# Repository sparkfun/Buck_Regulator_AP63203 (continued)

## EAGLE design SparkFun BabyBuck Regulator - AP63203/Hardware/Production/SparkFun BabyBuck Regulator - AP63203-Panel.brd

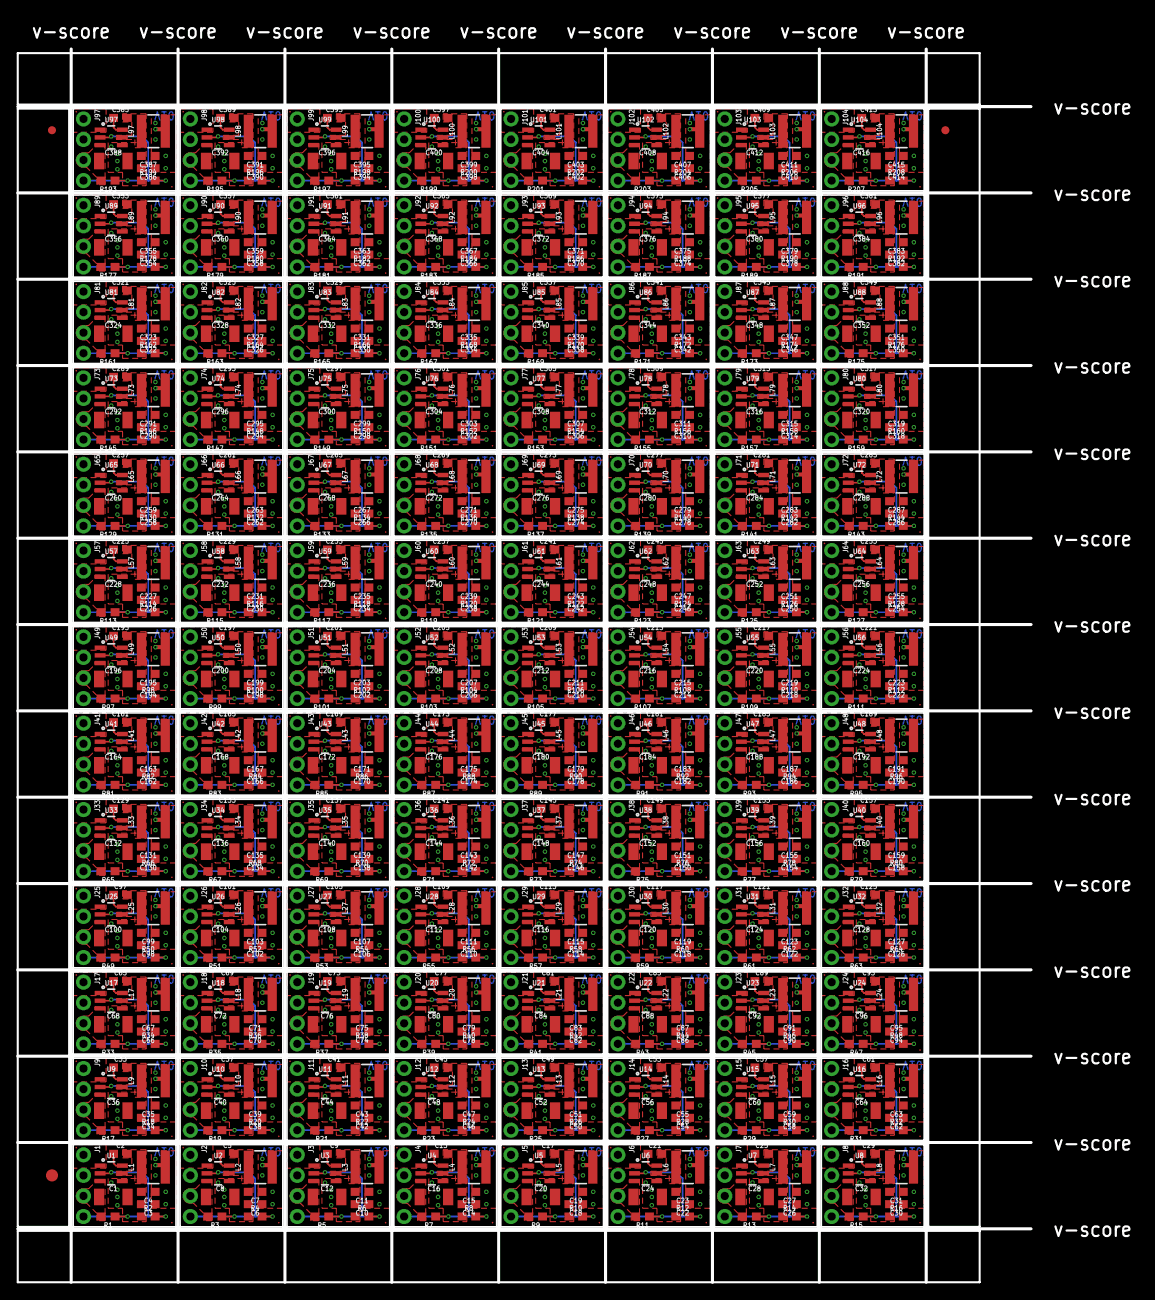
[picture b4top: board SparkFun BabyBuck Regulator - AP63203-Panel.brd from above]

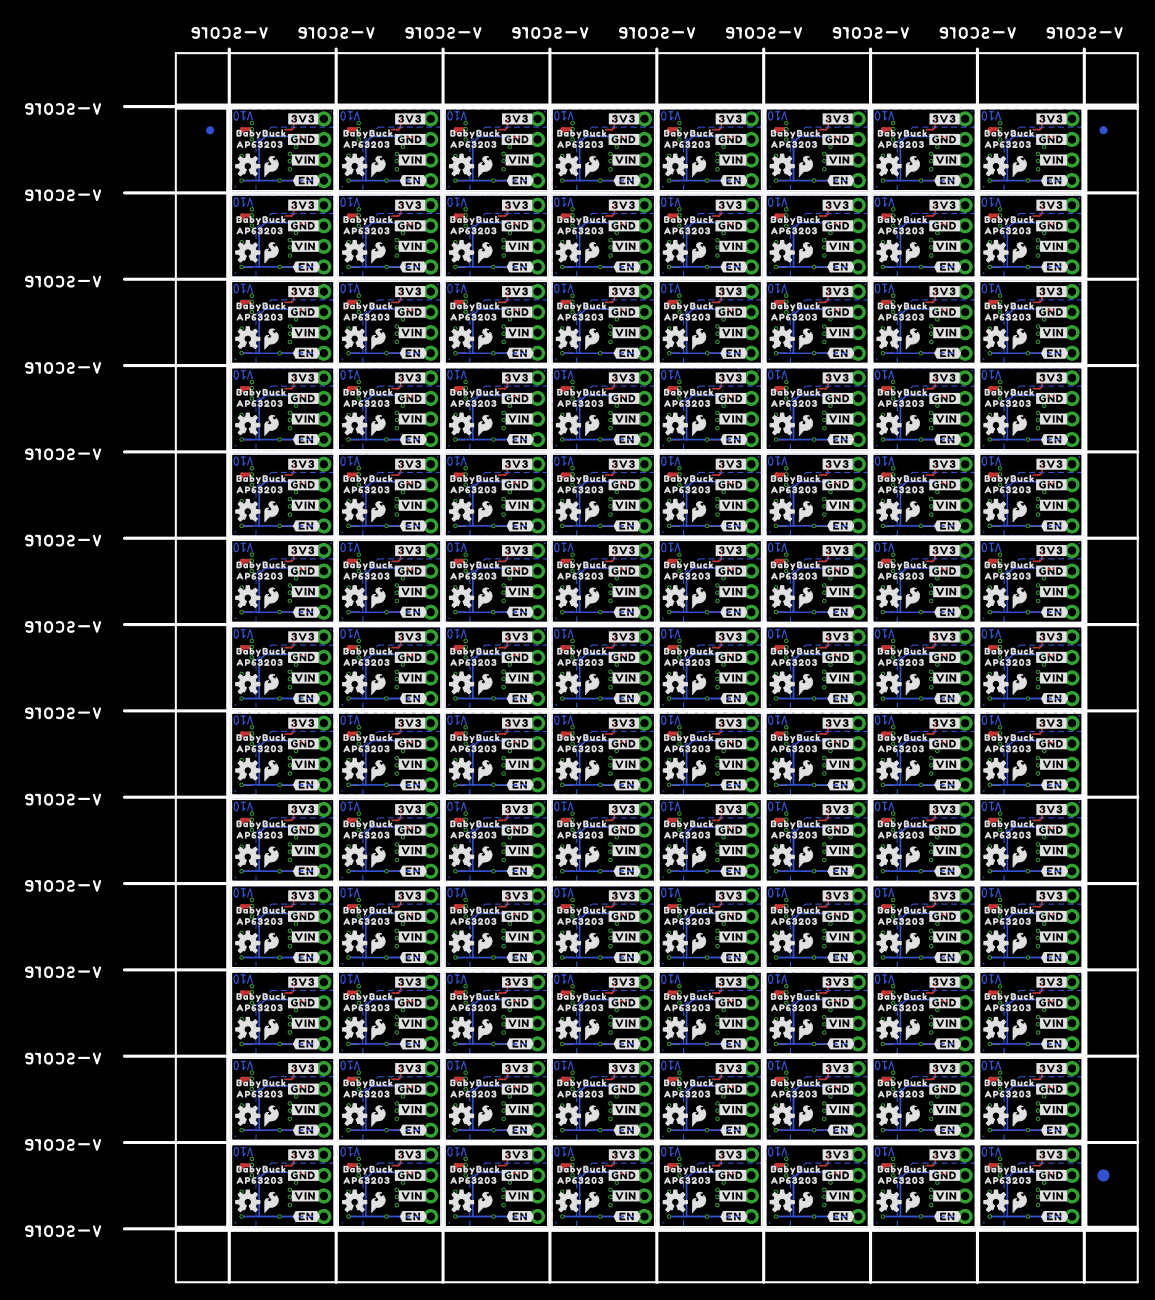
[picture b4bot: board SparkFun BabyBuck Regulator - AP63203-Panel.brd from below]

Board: 2 copper layers, 125.2 x 152.4 mm, 2190 parts (1043 on the bottom side), 624 nets.

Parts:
C1, C8, C12, C16, C20, C24, C28, C32, C36, C40, C44, C48, C52, C56, C60, C64, C68, C72, C76, C80, C84, C88, C92, C96, C100, C104, C108, C112, C116, C120, C124, C128, C132, C136, C140, C144, C148, C152, C156, C160, C164, C168, C172, C176, C180, C184, C188, C192, C196, C200, C204, C208, C212, C216, C220, C224, C228, C232, C236, C240, C244, C248, C252, C256, C260, C264, C268, C272, C276, C280, C284, C288, C292, C296, C300, C304, C308, C312, C316, C320, C324, C328, C332, C336, C340, C344, C348, C352, C356, C360, C364, C368, C372, C376, C380, C384, C388, C392, C396, C400, C404, C408, C412, C416: 10uF; 1210
C2, C5, C9, C13, C17, C21, C25, C29, C33, C37, C41, C45, C49, C53, C57, C61, C65, C69, C73, C77, C81, C85, C89, C93, C97, C101, C105, C109, C113, C117, C121, C125, C129, C133, C137, C141, C145, C149, C153, C157, C161, C165, C169, C173, C177, C181, C185, C189, C193, C197, C201, C205, C209, C213, C217, C221, C225, C229, C233, C237, C241, C245, C249, C253, C257, C261, C265, C269, C273, C277, C281, C285, C289, C293, C297, C301, C305, C309, C313, C317, C321, C325, C329, C333, C337, C341, C345, C349, C353, C357, C361, C365, C369, C373, C377, C381, C385, C389, C393, C397, C401, C405, C409, C413: 0.1uF; 0603
C3, C4, C6, C7, C10, C11, C14, C15, C18, C19, C22, C23, C26, C27, C30, C31, C34, C35, C38, C39, C42, C43, C46, C47, C50, C51, C54, C55, C58, C59, C62, C63, C66, C67, C70, C71, C74, C75, C78, C79, C82, C83, C86, C87, C90, C91, C94, C95, C98, C99, C102, C103, C106, C107, C110, C111, C114, C115, C118, C119, C122, C123, C126, C127, C130, C131, C134, C135, C138, C139, C142, C143, C146, C147, C150, C151, C154, C155, C158, C159, C162, C163, C166, C167, C170, C171, C174, C175, C178, C179, C182, C183, C186, C187, C190, C191, C194, C195, C198, C199, C202, C203, C206, C207, C210, C211, C214, C215, C218, C219, C222, C223, C226, C227, C230, C231, C234, C235, C238, C239, C242, C243, C246, C247, C250, C251, C254, C255, C258, C259, C262, C263, C266, C267, C270, C271, C274, C275, C278, C279, C282, C283, C286, C287, C290, C291, C294, C295, C298, C299, C302, C303, C306, C307, C310, C311, C314, C315, C318, C319, C322, C323, C326, C327, C330, C331, C334, C335, C338, C339, C342, C343, C346, C347, C350, C351, C354, C355, C358, C359, C362, C363, C366, C367, C370, C371, C374, C375, C378, C379, C382, C383, C386, C387, C390, C391, C394, C395, C398, C399, C402, C403, C406, C407, C410, C411, C414, C415: 22uF; 0603
E$1, E$2, E$3, E$4: FIDUCIAL-1X2
E$5, E$6: FIDUCIAL-1.5X3
FD1, FD2, FD3, FD4, FD5, FD6, FD7, FD8, FD9, FD10, FD11, FD12, FD13, FD14, FD15, FD16, FD17, FD18, FD19, FD20, FD21, FD22, FD23, FD24, FD25, FD26, FD27, FD28, FD29, FD30, FD31, FD32, FD33, FD34, FD35, FD36, FD37, FD38, FD39, FD40, FD41, FD42, FD43, FD44, FD45, FD46, FD47, FD48, FD49, FD50, FD51, FD52, FD53, FD54, FD55, FD56, FD57, FD58, FD59, FD60, FD61, FD62, FD63, FD64, FD65, FD66, FD67, FD68, FD69, FD70, FD71, FD72, FD73, FD74, FD75, FD76, FD77, FD78, FD79, FD80, FD81, FD82, FD83, FD84, FD85, FD86, FD87, FD88, FD89, FD90, FD91, FD92, FD93, FD94, FD95, FD96, FD97, FD98, FD99, FD100, FD101, FD102, FD103, FD104, FD105, FD106, FD107, FD108, FD109, FD110, FD111, FD112, FD113, FD114, FD115, FD116, FD117, FD118, FD119, FD120, FD121, FD122, FD123, FD124, FD125, FD126, FD127, FD128, FD129, FD130, FD131, FD132, FD133, FD134, FD135, FD136, FD137, FD138, FD139, FD140, FD141, FD142, FD143, FD144, FD145, FD146, FD147, FD148, FD149, FD150, FD151, FD152, FD153, FD154, FD155, FD156, FD157, FD158, FD159, FD160, FD161, FD162, FD163, FD164, FD165, FD166, FD167, FD168, FD169, FD170, FD171, FD172, FD173, FD174, FD175, FD176, FD177, FD178, FD179, FD180, FD181, FD182, FD183, FD184, FD185, FD186, FD187, FD188, FD189, FD190, FD191, FD192, FD193, FD194, FD195, FD196, FD197, FD198, FD199, FD200, FD201, FD202, FD203, FD204, FD205, FD206, FD207, FD208, FD209, FD210, FD211, FD212, FD213, FD214, FD215, FD216, FD217, FD218, FD219, FD220, FD221, FD222, FD223, FD224, FD225, FD226, FD227, FD228, FD229, FD230, FD231, FD232, FD233, FD234, FD235, FD236, FD237, FD238, FD239, FD240, FD241, FD242, FD243, FD244, FD245, FD246, FD247, FD248, FD249, FD250, FD251, FD252, FD253, FD254, FD255, FD256, FD257, FD258, FD259, FD260, FD261, FD262, FD263, FD264, FD265, FD266, FD267, FD268, FD269, FD270, FD271, FD272, FD273, FD274, FD275, FD276, FD277, FD278, FD279, FD280, FD281, FD282, FD283, FD284, FD285, FD286, FD287, FD288, FD289, FD290, FD291, FD292, FD293, FD294, FD295, FD296, FD297, FD298, FD299, FD300, FD301, FD302, FD303, FD304, FD305, FD306, FD307, FD308, FD309, FD310, FD311, FD312, FD313, FD314, FD315, FD316, FD317, FD318, FD319, FD320, FD321, FD322, FD323, FD324, FD325, FD326, FD327, FD328, FD329, FD330, FD331, FD332, FD333, FD334, FD335, FD336, FD337, FD338, FD339, FD340, FD341, FD342, FD343, FD344, FD345, FD346, FD347, FD348, FD349, FD350, FD351, FD352, FD353, FD354, FD355, FD356, FD357, FD358, FD359, FD360, FD361, FD362, FD363, FD364, FD365, FD366, FD367, FD368, FD369, FD370, FD371, FD372, FD373, FD374, FD375, FD376, FD377, FD378, FD379, FD380, FD381, FD382, FD383, FD384, FD385, FD386, FD387, FD388, FD389, FD390, FD391, FD392, FD393, FD394, FD395, FD396, FD397, FD398, FD399, FD400, FD401, FD402, FD403, FD404, FD405, FD406, FD407, FD408, FD409, FD410, FD411, FD412, FD413, FD414, FD415, FD416: FIDUCIAL0.2MM; FIDUCIAL-0.2MM
J1, J2, J3, J4, J5, J6, J7, J8, J9, J10, J11, J12, J13, J14, J15, J16, J17, J18, J19, J20, J21, J22, J23, J24, J25, J26, J27, J28, J29, J30, J31, J32, J33, J34, J35, J36, J37, J38, J39, J40, J41, J42, J43, J44, J45, J46, J47, J48, J49, J50, J51, J52, J53, J54, J55, J56, J57, J58, J59, J60, J61, J62, J63, J64, J65, J66, J67, J68, J69, J70, J71, J72, J73, J74, J75, J76, J77, J78, J79, J80, J81, J82, J83, J84, J85, J86, J87, J88, J89, J90, J91, J92, J93, J94, J95, J96, J97, J98, J99, J100, J101, J102, J103, J104: 1X04_NO_SILK
L1, L2, L3, L4, L5, L6, L7, L8, L9, L10, L11, L12, L13, L14, L15, L16, L17, L18, L19, L20, L21, L22, L23, L24, L25, L26, L27, L28, L29, L30, L31, L32, L33, L34, L35, L36, L37, L38, L39, L40, L41, L42, L43, L44, L45, L46, L47, L48, L49, L50, L51, L52, L53, L54, L55, L56, L57, L58, L59, L60, L61, L62, L63, L64, L65, L66, L67, L68, L69, L70, L71, L72, L73, L74, L75, L76, L77, L78, L79, L80, L81, L82, L83, L84, L85, L86, L87, L88, L89, L90, L91, L92, L93, L94, L95, L96, L97, L98, L99, L100, L101, L102, L103, L104: 4.7μH; INDUCTOR_4X4MM
LOGO1, LOGO3, LOGO5, LOGO7, LOGO9, LOGO11, LOGO13, LOGO15, LOGO17, LOGO19, LOGO21, LOGO23, LOGO25, LOGO27, LOGO29, LOGO31, LOGO33, LOGO35, LOGO37, LOGO39, LOGO41, LOGO43, LOGO45, LOGO47, LOGO49, LOGO51, LOGO53, LOGO55, LOGO57, LOGO59, LOGO61, LOGO63, LOGO65, LOGO67, LOGO69, LOGO71, LOGO73, LOGO75, LOGO77, LOGO79, LOGO81, LOGO83, LOGO85, LOGO87, LOGO89, LOGO91, LOGO93, LOGO95, LOGO97, LOGO99, LOGO101, LOGO103, LOGO105, LOGO107, LOGO109, LOGO111, LOGO113, LOGO115, LOGO117, LOGO119, LOGO121, LOGO123, LOGO125, LOGO127, LOGO129, LOGO131, LOGO133, LOGO135, LOGO137, LOGO139, LOGO141, LOGO143, LOGO145, LOGO147, LOGO149, LOGO151, LOGO153, LOGO155, LOGO157, LOGO159, LOGO161, LOGO163, LOGO165, LOGO167, LOGO169, LOGO171, LOGO173, LOGO175, LOGO177, LOGO179, LOGO181, LOGO183, LOGO185, LOGO187, LOGO189, LOGO191, LOGO193, LOGO195, LOGO197, LOGO199, LOGO201, LOGO203, LOGO205, LOGO207: SFE_LOGO_FLAME.1_INCH; SFE_LOGO_FLAME_.1
LOGO2, LOGO4, LOGO6, LOGO8, LOGO10, LOGO12, LOGO14, LOGO16, LOGO18, LOGO20, LOGO22, LOGO24, LOGO26, LOGO28, LOGO30, LOGO32, LOGO34, LOGO36, LOGO38, LOGO40, LOGO42, LOGO44, LOGO46, LOGO48, LOGO50, LOGO52, LOGO54, LOGO56, LOGO58, LOGO60, LOGO62, LOGO64, LOGO66, LOGO68, LOGO70, LOGO72, LOGO74, LOGO76, LOGO78, LOGO80, LOGO82, LOGO84, LOGO86, LOGO88, LOGO90, LOGO92, LOGO94, LOGO96, LOGO98, LOGO100, LOGO102, LOGO104, LOGO106, LOGO108, LOGO110, LOGO112, LOGO114, LOGO116, LOGO118, LOGO120, LOGO122, LOGO124, LOGO126, LOGO128, LOGO130, LOGO132, LOGO134, LOGO136, LOGO138, LOGO140, LOGO142, LOGO144, LOGO146, LOGO148, LOGO150, LOGO152, LOGO154, LOGO156, LOGO158, LOGO160, LOGO162, LOGO164, LOGO166, LOGO168, LOGO170, LOGO172, LOGO174, LOGO176, LOGO178, LOGO180, LOGO182, LOGO184, LOGO186, LOGO188, LOGO190, LOGO192, LOGO194, LOGO196, LOGO198, LOGO200, LOGO202, LOGO204, LOGO206, LOGO208: OSHW-LOGOS; OSHW-LOGO-S
R1, R2, R3, R4, R5, R6, R7, R8, R9, R10, R11, R12, R13, R14, R15, R16, R17, R18, R19, R20, R21, R22, R23, R24, R25, R26, R27, R28, R29, R30, R31, R32, R33, R34, R35, R36, R37, R38, R39, R40, R41, R42, R43, R44, R45, R46, R47, R48, R49, R50, R51, R52, R53, R54, R55, R56, R57, R58, R59, R60, R61, R62, R63, R64, R65, R66, R67, R68, R69, R70, R71, R72, R73, R74, R75, R76, R77, R78, R79, R80, R81, R82, R83, R84, R85, R86, R87, R88, R89, R90, R91, R92, R93, R94, R95, R96, R97, R98, R99, R100, R101, R102, R103, R104, R105, R106, R107, R108, R109, R110, R111, R112, R113, R114, R115, R116, R117, R118, R119, R120, R121, R122, R123, R124, R125, R126, R127, R128, R129, R130, R131, R132, R133, R134, R135, R136, R137, R138, R139, R140, R141, R142, R143, R144, R145, R146, R147, R148, R149, R150, R151, R152, R153, R154, R155, R156, R157, R158, R159, R160, R161, R162, R163, R164, R165, R166, R167, R168, R169, R170, R171, R172, R173, R174, R175, R176, R177, R178, R179, R180, R181, R182, R183, R184, R185, R186, R187, R188, R189, R190, R191, R192, R193, R194, R195, R196, R197, R198, R199, R200, R201, R202, R203, R204, R205, R206, R207, R208: 100k; 0603
U1, U2, U3, U4, U5, U6, U7, U8, U9, U10, U11, U12, U13, U14, U15, U16, U17, U18, U19, U20, U21, U22, U23, U24, U25, U26, U27, U28, U29, U30, U31, U32, U33, U34, U35, U36, U37, U38, U39, U40, U41, U42, U43, U44, U45, U46, U47, U48, U49, U50, U51, U52, U53, U54, U55, U56, U57, U58, U59, U60, U61, U62, U63, U64, U65, U66, U67, U68, U69, U70, U71, U72, U73, U74, U75, U76, U77, U78, U79, U80, U81, U82, U83, U84, U85, U86, U87, U88, U89, U90, U91, U92, U93, U94, U95, U96, U97, U98, U99, U100, U101, U102, U103, U104: AP63203; SOT23-6
U$1, U$5, U$13, U$19, U$25, U$31, U$37, U$43, U$49, U$55, U$61, U$67, U$73, U$79, U$85, U$91, U$97, U$103, U$109, U$115, U$121, U$127, U$133, U$139, U$145, U$151, U$157, U$163, U$169, U$175, U$181, U$187, U$193, U$199, U$205, U$211, U$217, U$223, U$229, U$235, U$241, U$247, U$253, U$259, U$265, U$271, U$277, U$283, U$289, U$295, U$301, U$307, U$313, U$319, U$325, U$331, U$337, U$343, U$349, U$355, U$361, U$367, U$373, U$379, U$385, U$391, U$397, U$403, U$409, U$415, U$421, U$427, U$433, U$439, U$445, U$451, U$457, U$463, U$469, U$475, U$481, U$487, U$493, U$499, U$505, U$511, U$517, U$523, U$529, U$535, U$541, U$547, U$553, U$559, U$565, U$571, U$577, U$583, U$589, U$595, U$601, U$607, U$613, U$619: #3V3#0
U$2, U$6, U$14, U$20, U$26, U$32, U$38, U$44, U$50, U$56, U$62, U$68, U$74, U$80, U$86, U$92, U$98, U$104, U$110, U$116, U$122, U$128, U$134, U$140, U$146, U$152, U$158, U$164, U$170, U$176, U$182, U$188, U$194, U$200, U$206, U$212, U$218, U$224, U$230, U$236, U$242, U$248, U$254, U$260, U$266, U$272, U$278, U$284, U$290, U$296, U$302, U$308, U$314, U$320, U$326, U$332, U$338, U$344, U$350, U$356, U$362, U$368, U$374, U$380, U$386, U$392, U$398, U$404, U$410, U$416, U$422, U$428, U$434, U$440, U$446, U$452, U$458, U$464, U$470, U$476, U$482, U$488, U$494, U$500, U$506, U$512, U$518, U$524, U$530, U$536, U$542, U$548, U$554, U$560, U$566, U$572, U$578, U$584, U$590, U$596, U$602, U$608, U$614, U$620: #GND#0
U$3, U$10, U$16, U$22, U$28, U$34, U$40, U$46, U$52, U$58, U$64, U$70, U$76, U$82, U$88, U$94, U$100, U$106, U$112, U$118, U$124, U$130, U$136, U$142, U$148, U$154, U$160, U$166, U$172, U$178, U$184, U$190, U$196, U$202, U$208, U$214, U$220, U$226, U$232, U$238, U$244, U$250, U$256, U$262, U$268, U$274, U$280, U$286, U$292, U$298, U$304, U$310, U$316, U$322, U$328, U$334, U$340, U$346, U$352, U$358, U$364, U$370, U$376, U$382, U$388, U$394, U$400, U$406, U$412, U$418, U$424, U$430, U$436, U$442, U$448, U$454, U$460, U$466, U$472, U$478, U$484, U$490, U$496, U$502, U$508, U$514, U$520, U$526, U$532, U$538, U$544, U$550, U$556, U$562, U$568, U$574, U$580, U$586, U$592, U$598, U$604, U$610, U$616, U$622: #VIN#0
U$4, U$9, U$15, U$21, U$27, U$33, U$39, U$45, U$51, U$57, U$63, U$69, U$75, U$81, U$87, U$93, U$99, U$105, U$111, U$117, U$123, U$129, U$135, U$141, U$147, U$153, U$159, U$165, U$171, U$177, U$183, U$189, U$195, U$201, U$207, U$213, U$219, U$225, U$231, U$237, U$243, U$249, U$255, U$261, U$267, U$273, U$279, U$285, U$291, U$297, U$303, U$309, U$315, U$321, U$327, U$333, U$339, U$345, U$351, U$357, U$363, U$369, U$375, U$381, U$387, U$393, U$399, U$405, U$411, U$417, U$423, U$429, U$435, U$441, U$447, U$453, U$459, U$465, U$471, U$477, U$483, U$489, U$495, U$501, U$507, U$513, U$519, U$525, U$531, U$537, U$543, U$549, U$555, U$561, U$567, U$573, U$579, U$585, U$591, U$597, U$603, U$609, U$615, U$621: #EN#0
U$7, U$11, U$17, U$23, U$29, U$35, U$41, U$47, U$53, U$59, U$65, U$71, U$77, U$83, U$89, U$95, U$101, U$107, U$113, U$119, U$125, U$131, U$137, U$143, U$149, U$155, U$161, U$167, U$173, U$179, U$185, U$191, U$197, U$203, U$209, U$215, U$221, U$227, U$233, U$239, U$245, U$251, U$257, U$263, U$269, U$275, U$281, U$287, U$293, U$299, U$305, U$311, U$317, U$323, U$329, U$335, U$341, U$347, U$353, U$359, U$365, U$371, U$377, U$383, U$389, U$395, U$401, U$407, U$413, U$419, U$425, U$431, U$437, U$443, U$449, U$455, U$461, U$467, U$473, U$479, U$485, U$491, U$497, U$503, U$509, U$515, U$521, U$527, U$533, U$539, U$545, U$551, U$557, U$563, U$569, U$575, U$581, U$587, U$593, U$599, U$605, U$611, U$617, U$623: AP632030
U$8, U$12, U$18, U$24, U$30, U$36, U$42, U$48, U$54, U$60, U$66, U$72, U$78, U$84, U$90, U$96, U$102, U$108, U$114, U$120, U$126, U$132, U$138, U$144, U$150, U$156, U$162, U$168, U$174, U$180, U$186, U$192, U$198, U$204, U$210, U$216, U$222, U$228, U$234, U$240, U$246, U$252, U$258, U$264, U$270, U$276, U$282, U$288, U$294, U$300, U$306, U$312, U$318, U$324, U$330, U$336, U$342, U$348, U$354, U$360, U$366, U$372, U$378, U$384, U$390, U$396, U$402, U$408, U$414, U$420, U$426, U$432, U$438, U$444, U$450, U$456, U$462, U$468, U$474, U$480, U$486, U$492, U$498, U$504, U$510, U$516, U$522, U$528, U$534, U$540, U$546, U$552, U$558, U$564, U$570, U$576, U$582, U$588, U$594, U$600, U$606, U$612, U$618, U$624: BABYBUCK0

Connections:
3.3V: C3.1, C4.1, J1.1, L1.P$2, U1.1
3.3V1: C6.1, C7.1, J2.1, L2.P$2, U2.1
3.3V2: C10.1, C11.1, J3.1, L3.P$2, U3.1
3.3V3: C14.1, C15.1, J4.1, L4.P$2, U4.1
3.3V4: C18.1, C19.1, J5.1, L5.P$2, U5.1
3.3V5: C22.1, C23.1, J6.1, L6.P$2, U6.1
3.3V6: C26.1, C27.1, J7.1, L7.P$2, U7.1
3.3V7: C30.1, C31.1, J8.1, L8.P$2, U8.1
3.3V8: C34.1, C35.1, J9.1, L9.P$2, U9.1
3.3V9: C38.1, C39.1, J10.1, L10.P$2, U10.1
3.3V10: C42.1, C43.1, J11.1, L11.P$2, U11.1
3.3V11: C46.1, C47.1, J12.1, L12.P$2, U12.1
3.3V12: C50.1, C51.1, J13.1, L13.P$2, U13.1
3.3V13: C54.1, C55.1, J14.1, L14.P$2, U14.1
3.3V14: C58.1, C59.1, J15.1, L15.P$2, U15.1
3.3V15: C62.1, C63.1, J16.1, L16.P$2, U16.1
3.3V16: C66.1, C67.1, J17.1, L17.P$2, U17.1
3.3V17: C70.1, C71.1, J18.1, L18.P$2, U18.1
3.3V18: C74.1, C75.1, J19.1, L19.P$2, U19.1
3.3V19: C78.1, C79.1, J20.1, L20.P$2, U20.1
3.3V20: C82.1, C83.1, J21.1, L21.P$2, U21.1
3.3V21: C86.1, C87.1, J22.1, L22.P$2, U22.1
3.3V22: C90.1, C91.1, J23.1, L23.P$2, U23.1
3.3V23: C94.1, C95.1, J24.1, L24.P$2, U24.1
3.3V24: C98.1, C99.1, J25.1, L25.P$2, U25.1
3.3V25: C102.1, C103.1, J26.1, L26.P$2, U26.1
3.3V26: C106.1, C107.1, J27.1, L27.P$2, U27.1
3.3V27: C110.1, C111.1, J28.1, L28.P$2, U28.1
3.3V28: C114.1, C115.1, J29.1, L29.P$2, U29.1
3.3V29: C118.1, C119.1, J30.1, L30.P$2, U30.1
3.3V30: C122.1, C123.1, J31.1, L31.P$2, U31.1
3.3V31: C126.1, C127.1, J32.1, L32.P$2, U32.1
3.3V32: C130.1, C131.1, J33.1, L33.P$2, U33.1
3.3V33: C134.1, C135.1, J34.1, L34.P$2, U34.1
3.3V34: C138.1, C139.1, J35.1, L35.P$2, U35.1
3.3V35: C142.1, C143.1, J36.1, L36.P$2, U36.1
3.3V36: C146.1, C147.1, J37.1, L37.P$2, U37.1
3.3V37: C150.1, C151.1, J38.1, L38.P$2, U38.1
3.3V38: C154.1, C155.1, J39.1, L39.P$2, U39.1
3.3V39: C158.1, C159.1, J40.1, L40.P$2, U40.1
3.3V40: C162.1, C163.1, J41.1, L41.P$2, U41.1
3.3V41: C166.1, C167.1, J42.1, L42.P$2, U42.1
3.3V42: C170.1, C171.1, J43.1, L43.P$2, U43.1
3.3V43: C174.1, C175.1, J44.1, L44.P$2, U44.1
3.3V44: C178.1, C179.1, J45.1, L45.P$2, U45.1
3.3V45: C182.1, C183.1, J46.1, L46.P$2, U46.1
3.3V46: C186.1, C187.1, J47.1, L47.P$2, U47.1
3.3V47: C190.1, C191.1, J48.1, L48.P$2, U48.1
3.3V48: C194.1, C195.1, J49.1, L49.P$2, U49.1
3.3V49: C198.1, C199.1, J50.1, L50.P$2, U50.1
3.3V50: C202.1, C203.1, J51.1, L51.P$2, U51.1
3.3V51: C206.1, C207.1, J52.1, L52.P$2, U52.1
3.3V52: C210.1, C211.1, J53.1, L53.P$2, U53.1
3.3V53: C214.1, C215.1, J54.1, L54.P$2, U54.1
3.3V54: C218.1, C219.1, J55.1, L55.P$2, U55.1
3.3V55: C222.1, C223.1, J56.1, L56.P$2, U56.1
3.3V56: C226.1, C227.1, J57.1, L57.P$2, U57.1
3.3V57: C230.1, C231.1, J58.1, L58.P$2, U58.1
3.3V58: C234.1, C235.1, J59.1, L59.P$2, U59.1
3.3V59: C238.1, C239.1, J60.1, L60.P$2, U60.1
3.3V60: C242.1, C243.1, J61.1, L61.P$2, U61.1
3.3V61: C246.1, C247.1, J62.1, L62.P$2, U62.1
3.3V62: C250.1, C251.1, J63.1, L63.P$2, U63.1
3.3V63: C254.1, C255.1, J64.1, L64.P$2, U64.1
3.3V64: C258.1, C259.1, J65.1, L65.P$2, U65.1
3.3V65: C262.1, C263.1, J66.1, L66.P$2, U66.1
3.3V66: C266.1, C267.1, J67.1, L67.P$2, U67.1
3.3V67: C270.1, C271.1, J68.1, L68.P$2, U68.1
3.3V68: C274.1, C275.1, J69.1, L69.P$2, U69.1
3.3V69: C278.1, C279.1, J70.1, L70.P$2, U70.1
3.3V70: C282.1, C283.1, J71.1, L71.P$2, U71.1
3.3V71: C286.1, C287.1, J72.1, L72.P$2, U72.1
3.3V72: C290.1, C291.1, J73.1, L73.P$2, U73.1
3.3V73: C294.1, C295.1, J74.1, L74.P$2, U74.1
3.3V74: C298.1, C299.1, J75.1, L75.P$2, U75.1
3.3V75: C302.1, C303.1, J76.1, L76.P$2, U76.1
3.3V76: C306.1, C307.1, J77.1, L77.P$2, U77.1
3.3V77: C310.1, C311.1, J78.1, L78.P$2, U78.1
3.3V78: C314.1, C315.1, J79.1, L79.P$2, U79.1
3.3V79: C318.1, C319.1, J80.1, L80.P$2, U80.1
3.3V80: C322.1, C323.1, J81.1, L81.P$2, U81.1
3.3V81: C326.1, C327.1, J82.1, L82.P$2, U82.1
3.3V82: C330.1, C331.1, J83.1, L83.P$2, U83.1
3.3V83: C334.1, C335.1, J84.1, L84.P$2, U84.1
3.3V84: C338.1, C339.1, J85.1, L85.P$2, U85.1
3.3V85: C342.1, C343.1, J86.1, L86.P$2, U86.1
3.3V86: C346.1, C347.1, J87.1, L87.P$2, U87.1
3.3V87: C350.1, C351.1, J88.1, L88.P$2, U88.1
3.3V88: C354.1, C355.1, J89.1, L89.P$2, U89.1
3.3V89: C358.1, C359.1, J90.1, L90.P$2, U90.1
3.3V90: C362.1, C363.1, J91.1, L91.P$2, U91.1
3.3V91: C366.1, C367.1, J92.1, L92.P$2, U92.1
3.3V92: C370.1, C371.1, J93.1, L93.P$2, U93.1
3.3V93: C374.1, C375.1, J94.1, L94.P$2, U94.1
3.3V94: C378.1, C379.1, J95.1, L95.P$2, U95.1
3.3V95: C382.1, C383.1, J96.1, L96.P$2, U96.1
3.3V96: C386.1, C387.1, J97.1, L97.P$2, U97.1
3.3V97: C390.1, C391.1, J98.1, L98.P$2, U98.1
3.3V98: C394.1, C395.1, J99.1, L99.P$2, U99.1
3.3V99: C398.1, C399.1, J100.1, L100.P$2, U100.1
3.3V100: C402.1, C403.1, J101.1, L101.P$2, U101.1
3.3V101: C406.1, C407.1, J102.1, L102.P$2, U102.1
3.3V102: C410.1, C411.1, J103.1, L103.P$2, U103.1
3.3V103: C414.1, C415.1, J104.1, L104.P$2, U104.1
EN: J1.4, R1.1, R2.2, U1.2
EN1: J2.4, R3.1, R4.2, U2.2
EN2: J3.4, R5.1, R6.2, U3.2
EN3: J4.4, R7.1, R8.2, U4.2
EN4: J5.4, R9.1, R10.2, U5.2
EN5: J6.4, R11.1, R12.2, U6.2
EN6: J7.4, R13.1, R14.2, U7.2
EN7: J8.4, R15.1, R16.2, U8.2
EN8: J9.4, R17.1, R18.2, U9.2
EN9: J10.4, R19.1, R20.2, U10.2
EN10: J11.4, R21.1, R22.2, U11.2
EN11: J12.4, R23.1, R24.2, U12.2
EN12: J13.4, R25.1, R26.2, U13.2
EN13: J14.4, R27.1, R28.2, U14.2
EN14: J15.4, R29.1, R30.2, U15.2
EN15: J16.4, R31.1, R32.2, U16.2
EN16: J17.4, R33.1, R34.2, U17.2
EN17: J18.4, R35.1, R36.2, U18.2
EN18: J19.4, R37.1, R38.2, U19.2
EN19: J20.4, R39.1, R40.2, U20.2
EN20: J21.4, R41.1, R42.2, U21.2
EN21: J22.4, R43.1, R44.2, U22.2
EN22: J23.4, R45.1, R46.2, U23.2
EN23: J24.4, R47.1, R48.2, U24.2
EN24: J25.4, R49.1, R50.2, U25.2
EN25: J26.4, R51.1, R52.2, U26.2
EN26: J27.4, R53.1, R54.2, U27.2
EN27: J28.4, R55.1, R56.2, U28.2
EN28: J29.4, R57.1, R58.2, U29.2
EN29: J30.4, R59.1, R60.2, U30.2
EN30: J31.4, R61.1, R62.2, U31.2
EN31: J32.4, R63.1, R64.2, U32.2
EN32: J33.4, R65.1, R66.2, U33.2
EN33: J34.4, R67.1, R68.2, U34.2
EN34: J35.4, R69.1, R70.2, U35.2
EN35: J36.4, R71.1, R72.2, U36.2
EN36: J37.4, R73.1, R74.2, U37.2
EN37: J38.4, R75.1, R76.2, U38.2
EN38: J39.4, R77.1, R78.2, U39.2
EN39: J40.4, R79.1, R80.2, U40.2
EN40: J41.4, R81.1, R82.2, U41.2
EN41: J42.4, R83.1, R84.2, U42.2
EN42: J43.4, R85.1, R86.2, U43.2
EN43: J44.4, R87.1, R88.2, U44.2
EN44: J45.4, R89.1, R90.2, U45.2
EN45: J46.4, R91.1, R92.2, U46.2
EN46: J47.4, R93.1, R94.2, U47.2
EN47: J48.4, R95.1, R96.2, U48.2
EN48: J49.4, R97.1, R98.2, U49.2
EN49: J50.4, R99.1, R100.2, U50.2
EN50: J51.4, R101.1, R102.2, U51.2
EN51: J52.4, R103.1, R104.2, U52.2
EN52: J53.4, R105.1, R106.2, U53.2
EN53: J54.4, R107.1, R108.2, U54.2
EN54: J55.4, R109.1, R110.2, U55.2
EN55: J56.4, R111.1, R112.2, U56.2
EN56: J57.4, R113.1, R114.2, U57.2
EN57: J58.4, R115.1, R116.2, U58.2
EN58: J59.4, R117.1, R118.2, U59.2
EN59: J60.4, R119.1, R120.2, U60.2
EN60: J61.4, R121.1, R122.2, U61.2
EN61: J62.4, R123.1, R124.2, U62.2
EN62: J63.4, R125.1, R126.2, U63.2
EN63: J64.4, R127.1, R128.2, U64.2
EN64: J65.4, R129.1, R130.2, U65.2
EN65: J66.4, R131.1, R132.2, U66.2
EN66: J67.4, R133.1, R134.2, U67.2
EN67: J68.4, R135.1, R136.2, U68.2
EN68: J69.4, R137.1, R138.2, U69.2
EN69: J70.4, R139.1, R140.2, U70.2
EN70: J71.4, R141.1, R142.2, U71.2
EN71: J72.4, R143.1, R144.2, U72.2
EN72: J73.4, R145.1, R146.2, U73.2
EN73: J74.4, R147.1, R148.2, U74.2
EN74: J75.4, R149.1, R150.2, U75.2
EN75: J76.4, R151.1, R152.2, U76.2
EN76: J77.4, R153.1, R154.2, U77.2
EN77: J78.4, R155.1, R156.2, U78.2
EN78: J79.4, R157.1, R158.2, U79.2
EN79: J80.4, R159.1, R160.2, U80.2
EN80: J81.4, R161.1, R162.2, U81.2
EN81: J82.4, R163.1, R164.2, U82.2
EN82: J83.4, R165.1, R166.2, U83.2
EN83: J84.4, R167.1, R168.2, U84.2
EN84: J85.4, R169.1, R170.2, U85.2
EN85: J86.4, R171.1, R172.2, U86.2
EN86: J87.4, R173.1, R174.2, U87.2
EN87: J88.4, R175.1, R176.2, U88.2
EN88: J89.4, R177.1, R178.2, U89.2
EN89: J90.4, R179.1, R180.2, U90.2
EN90: J91.4, R181.1, R182.2, U91.2
EN91: J92.4, R183.1, R184.2, U92.2
EN92: J93.4, R185.1, R186.2, U93.2
EN93: J94.4, R187.1, R188.2, U94.2
EN94: J95.4, R189.1, R190.2, U95.2
EN95: J96.4, R191.1, R192.2, U96.2
EN96: J97.4, R193.1, R194.2, U97.2
EN97: J98.4, R195.1, R196.2, U98.2
EN98: J99.4, R197.1, R198.2, U99.2
EN99: J100.4, R199.1, R200.2, U100.2
EN100: J101.4, R201.1, R202.2, U101.2
EN101: J102.4, R203.1, R204.2, U102.2
EN102: J103.4, R205.1, R206.2, U103.2
EN103: J104.4, R207.1, R208.2, U104.2
GND: C1.2, C3.2, C4.2, J1.2, R2.1, U1.4
GND1: C6.2, C7.2, C8.2, J2.2, R4.1, U2.4
GND2: C10.2, C11.2, C12.2, J3.2, R6.1, U3.4
GND3: C14.2, C15.2, C16.2, J4.2, R8.1, U4.4
GND4: C18.2, C19.2, C20.2, J5.2, R10.1, U5.4
GND5: C22.2, C23.2, C24.2, J6.2, R12.1, U6.4
GND6: C26.2, C27.2, C28.2, J7.2, R14.1, U7.4
GND7: C30.2, C31.2, C32.2, J8.2, R16.1, U8.4
GND8: C34.2, C35.2, C36.2, J9.2, R18.1, U9.4
GND9: C38.2, C39.2, C40.2, J10.2, R20.1, U10.4
GND10: C42.2, C43.2, C44.2, J11.2, R22.1, U11.4
GND11: C46.2, C47.2, C48.2, J12.2, R24.1, U12.4
GND12: C50.2, C51.2, C52.2, J13.2, R26.1, U13.4
GND13: C54.2, C55.2, C56.2, J14.2, R28.1, U14.4
GND14: C58.2, C59.2, C60.2, J15.2, R30.1, U15.4
GND15: C62.2, C63.2, C64.2, J16.2, R32.1, U16.4
GND16: C66.2, C67.2, C68.2, J17.2, R34.1, U17.4
GND17: C70.2, C71.2, C72.2, J18.2, R36.1, U18.4
GND18: C74.2, C75.2, C76.2, J19.2, R38.1, U19.4
GND19: C78.2, C79.2, C80.2, J20.2, R40.1, U20.4
GND20: C82.2, C83.2, C84.2, J21.2, R42.1, U21.4
GND21: C86.2, C87.2, C88.2, J22.2, R44.1, U22.4
GND22: C90.2, C91.2, C92.2, J23.2, R46.1, U23.4
GND23: C94.2, C95.2, C96.2, J24.2, R48.1, U24.4
GND24: C98.2, C99.2, C100.2, J25.2, R50.1, U25.4
GND25: C102.2, C103.2, C104.2, J26.2, R52.1, U26.4
GND26: C106.2, C107.2, C108.2, J27.2, R54.1, U27.4
GND27: C110.2, C111.2, C112.2, J28.2, R56.1, U28.4
GND28: C114.2, C115.2, C116.2, J29.2, R58.1, U29.4
GND29: C118.2, C119.2, C120.2, J30.2, R60.1, U30.4
GND30: C122.2, C123.2, C124.2, J31.2, R62.1, U31.4
GND31: C126.2, C127.2, C128.2, J32.2, R64.1, U32.4
GND32: C130.2, C131.2, C132.2, J33.2, R66.1, U33.4
GND33: C134.2, C135.2, C136.2, J34.2, R68.1, U34.4
GND34: C138.2, C139.2, C140.2, J35.2, R70.1, U35.4
GND35: C142.2, C143.2, C144.2, J36.2, R72.1, U36.4
GND36: C146.2, C147.2, C148.2, J37.2, R74.1, U37.4
GND37: C150.2, C151.2, C152.2, J38.2, R76.1, U38.4
GND38: C154.2, C155.2, C156.2, J39.2, R78.1, U39.4
GND39: C158.2, C159.2, C160.2, J40.2, R80.1, U40.4
GND40: C162.2, C163.2, C164.2, J41.2, R82.1, U41.4
GND41: C166.2, C167.2, C168.2, J42.2, R84.1, U42.4
GND42: C170.2, C171.2, C172.2, J43.2, R86.1, U43.4
GND43: C174.2, C175.2, C176.2, J44.2, R88.1, U44.4
GND44: C178.2, C179.2, C180.2, J45.2, R90.1, U45.4
GND45: C182.2, C183.2, C184.2, J46.2, R92.1, U46.4
GND46: C186.2, C187.2, C188.2, J47.2, R94.1, U47.4
GND47: C190.2, C191.2, C192.2, J48.2, R96.1, U48.4
GND48: C194.2, C195.2, C196.2, J49.2, R98.1, U49.4
GND49: C198.2, C199.2, C200.2, J50.2, R100.1, U50.4
GND50: C202.2, C203.2, C204.2, J51.2, R102.1, U51.4
GND51: C206.2, C207.2, C208.2, J52.2, R104.1, U52.4
GND52: C210.2, C211.2, C212.2, J53.2, R106.1, U53.4
GND53: C214.2, C215.2, C216.2, J54.2, R108.1, U54.4
GND54: C218.2, C219.2, C220.2, J55.2, R110.1, U55.4
GND55: C222.2, C223.2, C224.2, J56.2, R112.1, U56.4
GND56: C226.2, C227.2, C228.2, J57.2, R114.1, U57.4
GND57: C230.2, C231.2, C232.2, J58.2, R116.1, U58.4
GND58: C234.2, C235.2, C236.2, J59.2, R118.1, U59.4
GND59: C238.2, C239.2, C240.2, J60.2, R120.1, U60.4
GND60: C242.2, C243.2, C244.2, J61.2, R122.1, U61.4
GND61: C246.2, C247.2, C248.2, J62.2, R124.1, U62.4
GND62: C250.2, C251.2, C252.2, J63.2, R126.1, U63.4
GND63: C254.2, C255.2, C256.2, J64.2, R128.1, U64.4
GND64: C258.2, C259.2, C260.2, J65.2, R130.1, U65.4
GND65: C262.2, C263.2, C264.2, J66.2, R132.1, U66.4
GND66: C266.2, C267.2, C268.2, J67.2, R134.1, U67.4
GND67: C270.2, C271.2, C272.2, J68.2, R136.1, U68.4
GND68: C274.2, C275.2, C276.2, J69.2, R138.1, U69.4
GND69: C278.2, C279.2, C280.2, J70.2, R140.1, U70.4
GND70: C282.2, C283.2, C284.2, J71.2, R142.1, U71.4
GND71: C286.2, C287.2, C288.2, J72.2, R144.1, U72.4
GND72: C290.2, C291.2, C292.2, J73.2, R146.1, U73.4
GND73: C294.2, C295.2, C296.2, J74.2, R148.1, U74.4
GND74: C298.2, C299.2, C300.2, J75.2, R150.1, U75.4
GND75: C302.2, C303.2, C304.2, J76.2, R152.1, U76.4
GND76: C306.2, C307.2, C308.2, J77.2, R154.1, U77.4
GND77: C310.2, C311.2, C312.2, J78.2, R156.1, U78.4
GND78: C314.2, C315.2, C316.2, J79.2, R158.1, U79.4
GND79: C318.2, C319.2, C320.2, J80.2, R160.1, U80.4
GND80: C322.2, C323.2, C324.2, J81.2, R162.1, U81.4
GND81: C326.2, C327.2, C328.2, J82.2, R164.1, U82.4
GND82: C330.2, C331.2, C332.2, J83.2, R166.1, U83.4
GND83: C334.2, C335.2, C336.2, J84.2, R168.1, U84.4
GND84: C338.2, C339.2, C340.2, J85.2, R170.1, U85.4
GND85: C342.2, C343.2, C344.2, J86.2, R172.1, U86.4
GND86: C346.2, C347.2, C348.2, J87.2, R174.1, U87.4
GND87: C350.2, C351.2, C352.2, J88.2, R176.1, U88.4
GND88: C354.2, C355.2, C356.2, J89.2, R178.1, U89.4
GND89: C358.2, C359.2, C360.2, J90.2, R180.1, U90.4
GND90: C362.2, C363.2, C364.2, J91.2, R182.1, U91.4
GND91: C366.2, C367.2, C368.2, J92.2, R184.1, U92.4
GND92: C370.2, C371.2, C372.2, J93.2, R186.1, U93.4
GND93: C374.2, C375.2, C376.2, J94.2, R188.1, U94.4
GND94: C378.2, C379.2, C380.2, J95.2, R190.1, U95.4
GND95: C382.2, C383.2, C384.2, J96.2, R192.1, U96.4
GND96: C386.2, C387.2, C388.2, J97.2, R194.1, U97.4
GND97: C390.2, C391.2, C392.2, J98.2, R196.1, U98.4
GND98: C394.2, C395.2, C396.2, J99.2, R198.1, U99.4
GND99: C398.2, C399.2, C400.2, J100.2, R200.1, U100.4
GND100: C402.2, C403.2, C404.2, J101.2, R202.1, U101.4
GND101: C406.2, C407.2, C408.2, J102.2, R204.1, U102.4
GND102: C410.2, C411.2, C412.2, J103.2, R206.1, U103.4
GND103: C414.2, C415.2, C416.2, J104.2, R208.1, U104.4
unnamed: C5.1, U2.6
unnamed: C5.2, L2.P$1, U2.5
unnamed: C9.1, U3.6
unnamed: C2.1, U1.6
unnamed: C2.2, L1.P$1, U1.5
unnamed: C9.2, L3.P$1, U3.5
unnamed: C13.1, U4.6
unnamed: C13.2, L4.P$1, U4.5
unnamed: C17.1, U5.6
unnamed: C17.2, L5.P$1, U5.5
unnamed: C21.1, U6.6
unnamed: C21.2, L6.P$1, U6.5
unnamed: C25.1, U7.6
unnamed: C25.2, L7.P$1, U7.5
unnamed: C29.1, U8.6
unnamed: C29.2, L8.P$1, U8.5
unnamed: C33.1, U9.6
unnamed: C33.2, L9.P$1, U9.5
unnamed: C37.1, U10.6
unnamed: C37.2, L10.P$1, U10.5
unnamed: C41.1, U11.6
unnamed: C41.2, L11.P$1, U11.5
unnamed: C45.1, U12.6
unnamed: C45.2, L12.P$1, U12.5
unnamed: C49.1, U13.6
unnamed: C49.2, L13.P$1, U13.5
unnamed: C53.1, U14.6
unnamed: C53.2, L14.P$1, U14.5
unnamed: C57.1, U15.6
unnamed: C57.2, L15.P$1, U15.5
unnamed: C61.1, U16.6
unnamed: C61.2, L16.P$1, U16.5
unnamed: C65.1, U17.6
unnamed: C65.2, L17.P$1, U17.5
unnamed: C69.1, U18.6
unnamed: C69.2, L18.P$1, U18.5
unnamed: C73.1, U19.6
unnamed: C73.2, L19.P$1, U19.5
unnamed: C77.1, U20.6
unnamed: C77.2, L20.P$1, U20.5
unnamed: C81.1, U21.6
unnamed: C81.2, L21.P$1, U21.5
unnamed: C85.1, U22.6
unnamed: C85.2, L22.P$1, U22.5
unnamed: C89.1, U23.6
unnamed: C89.2, L23.P$1, U23.5
unnamed: C93.1, U24.6
unnamed: C93.2, L24.P$1, U24.5
unnamed: C97.1, U25.6
unnamed: C97.2, L25.P$1, U25.5
unnamed: C101.1, U26.6
unnamed: C101.2, L26.P$1, U26.5
unnamed: C105.1, U27.6
unnamed: C105.2, L27.P$1, U27.5
unnamed: C109.1, U28.6
unnamed: C109.2, L28.P$1, U28.5
unnamed: C113.1, U29.6
unnamed: C113.2, L29.P$1, U29.5
unnamed: C117.1, U30.6
unnamed: C117.2, L30.P$1, U30.5
unnamed: C121.1, U31.6
unnamed: C121.2, L31.P$1, U31.5
unnamed: C125.1, U32.6
unnamed: C125.2, L32.P$1, U32.5
unnamed: C129.1, U33.6
unnamed: C129.2, L33.P$1, U33.5
unnamed: C133.1, U34.6
unnamed: C133.2, L34.P$1, U34.5
unnamed: C137.1, U35.6
unnamed: C137.2, L35.P$1, U35.5
unnamed: C141.1, U36.6
unnamed: C141.2, L36.P$1, U36.5
unnamed: C145.1, U37.6
unnamed: C145.2, L37.P$1, U37.5
unnamed: C149.1, U38.6
unnamed: C149.2, L38.P$1, U38.5
unnamed: C153.1, U39.6
unnamed: C153.2, L39.P$1, U39.5
unnamed: C157.1, U40.6
unnamed: C157.2, L40.P$1, U40.5
unnamed: C161.1, U41.6
unnamed: C161.2, L41.P$1, U41.5
unnamed: C165.1, U42.6
unnamed: C165.2, L42.P$1, U42.5
unnamed: C169.1, U43.6
unnamed: C169.2, L43.P$1, U43.5
unnamed: C173.1, U44.6
unnamed: C173.2, L44.P$1, U44.5
unnamed: C177.1, U45.6
unnamed: C177.2, L45.P$1, U45.5
unnamed: C181.1, U46.6
unnamed: C181.2, L46.P$1, U46.5
unnamed: C185.1, U47.6
unnamed: C185.2, L47.P$1, U47.5
unnamed: C189.1, U48.6
unnamed: C189.2, L48.P$1, U48.5
unnamed: C193.1, U49.6
unnamed: C193.2, L49.P$1, U49.5
unnamed: C197.1, U50.6
unnamed: C197.2, L50.P$1, U50.5
unnamed: C201.1, U51.6
unnamed: C201.2, L51.P$1, U51.5
unnamed: C205.1, U52.6
unnamed: C205.2, L52.P$1, U52.5
unnamed: C209.1, U53.6
unnamed: C209.2, L53.P$1, U53.5
unnamed: C213.1, U54.6
unnamed: C213.2, L54.P$1, U54.5
unnamed: C217.1, U55.6
unnamed: C217.2, L55.P$1, U55.5
unnamed: C221.1, U56.6
unnamed: C221.2, L56.P$1, U56.5
unnamed: C225.1, U57.6
unnamed: C225.2, L57.P$1, U57.5
unnamed: C229.1, U58.6
unnamed: C229.2, L58.P$1, U58.5
unnamed: C233.1, U59.6
unnamed: C233.2, L59.P$1, U59.5
unnamed: C237.1, U60.6
unnamed: C237.2, L60.P$1, U60.5
unnamed: C241.1, U61.6
unnamed: C241.2, L61.P$1, U61.5
unnamed: C245.1, U62.6
unnamed: C245.2, L62.P$1, U62.5
unnamed: C249.1, U63.6
unnamed: C249.2, L63.P$1, U63.5
unnamed: C253.1, U64.6
unnamed: C253.2, L64.P$1, U64.5
unnamed: C257.1, U65.6
unnamed: C257.2, L65.P$1, U65.5
unnamed: C261.1, U66.6
unnamed: C261.2, L66.P$1, U66.5
unnamed: C265.1, U67.6
unnamed: C265.2, L67.P$1, U67.5
unnamed: C269.1, U68.6
unnamed: C269.2, L68.P$1, U68.5
unnamed: C273.1, U69.6
unnamed: C273.2, L69.P$1, U69.5
unnamed: C277.1, U70.6
unnamed: C277.2, L70.P$1, U70.5
unnamed: C281.1, U71.6
unnamed: C281.2, L71.P$1, U71.5
unnamed: C285.1, U72.6
unnamed: C285.2, L72.P$1, U72.5
unnamed: C289.1, U73.6
unnamed: C289.2, L73.P$1, U73.5
unnamed: C293.1, U74.6
unnamed: C293.2, L74.P$1, U74.5
unnamed: C297.1, U75.6
unnamed: C297.2, L75.P$1, U75.5
unnamed: C301.1, U76.6
unnamed: C301.2, L76.P$1, U76.5
unnamed: C305.1, U77.6
unnamed: C305.2, L77.P$1, U77.5
unnamed: C309.1, U78.6
unnamed: C309.2, L78.P$1, U78.5
unnamed: C313.1, U79.6
unnamed: C313.2, L79.P$1, U79.5
unnamed: C317.1, U80.6
unnamed: C317.2, L80.P$1, U80.5
unnamed: C321.1, U81.6
unnamed: C321.2, L81.P$1, U81.5
unnamed: C325.1, U82.6
unnamed: C325.2, L82.P$1, U82.5
unnamed: C329.1, U83.6
unnamed: C329.2, L83.P$1, U83.5
unnamed: C333.1, U84.6
unnamed: C333.2, L84.P$1, U84.5
unnamed: C337.1, U85.6
unnamed: C337.2, L85.P$1, U85.5
unnamed: C341.1, U86.6
unnamed: C341.2, L86.P$1, U86.5
unnamed: C345.1, U87.6
unnamed: C345.2, L87.P$1, U87.5
unnamed: C349.1, U88.6
unnamed: C349.2, L88.P$1, U88.5
unnamed: C353.1, U89.6
unnamed: C353.2, L89.P$1, U89.5
unnamed: C357.1, U90.6
unnamed: C357.2, L90.P$1, U90.5
unnamed: C361.1, U91.6
unnamed: C361.2, L91.P$1, U91.5
unnamed: C365.1, U92.6
unnamed: C365.2, L92.P$1, U92.5
unnamed: C369.1, U93.6
unnamed: C369.2, L93.P$1, U93.5
unnamed: C373.1, U94.6
unnamed: C373.2, L94.P$1, U94.5
unnamed: C377.1, U95.6
unnamed: C377.2, L95.P$1, U95.5
unnamed: C381.1, U96.6
unnamed: C381.2, L96.P$1, U96.5
unnamed: C385.1, U97.6
unnamed: C385.2, L97.P$1, U97.5
unnamed: C389.1, U98.6
unnamed: C389.2, L98.P$1, U98.5
unnamed: C393.1, U99.6
unnamed: C393.2, L99.P$1, U99.5
unnamed: C397.1, U100.6
unnamed: C397.2, L100.P$1, U100.5
unnamed: C401.1, U101.6
unnamed: C401.2, L101.P$1, U101.5
unnamed: C405.1, U102.6
unnamed: C405.2, L102.P$1, U102.5
unnamed: C409.1, U103.6
unnamed: C409.2, L103.P$1, U103.5
unnamed: C413.1, U104.6
unnamed: C413.2, L104.P$1, U104.5
VIN: C1.1, J1.3, R1.2, U1.3
VIN1: C8.1, J2.3, R3.2, U2.3
VIN2: C12.1, J3.3, R5.2, U3.3
VIN3: C16.1, J4.3, R7.2, U4.3
VIN4: C20.1, J5.3, R9.2, U5.3
VIN5: C24.1, J6.3, R11.2, U6.3
VIN6: C28.1, J7.3, R13.2, U7.3
VIN7: C32.1, J8.3, R15.2, U8.3
VIN8: C36.1, J9.3, R17.2, U9.3
VIN9: C40.1, J10.3, R19.2, U10.3
VIN10: C44.1, J11.3, R21.2, U11.3
VIN11: C48.1, J12.3, R23.2, U12.3
VIN12: C52.1, J13.3, R25.2, U13.3
VIN13: C56.1, J14.3, R27.2, U14.3
VIN14: C60.1, J15.3, R29.2, U15.3
VIN15: C64.1, J16.3, R31.2, U16.3
VIN16: C68.1, J17.3, R33.2, U17.3
VIN17: C72.1, J18.3, R35.2, U18.3
VIN18: C76.1, J19.3, R37.2, U19.3
VIN19: C80.1, J20.3, R39.2, U20.3
VIN20: C84.1, J21.3, R41.2, U21.3
VIN21: C88.1, J22.3, R43.2, U22.3
VIN22: C92.1, J23.3, R45.2, U23.3
VIN23: C96.1, J24.3, R47.2, U24.3
VIN24: C100.1, J25.3, R49.2, U25.3
VIN25: C104.1, J26.3, R51.2, U26.3
VIN26: C108.1, J27.3, R53.2, U27.3
VIN27: C112.1, J28.3, R55.2, U28.3
VIN28: C116.1, J29.3, R57.2, U29.3
VIN29: C120.1, J30.3, R59.2, U30.3
VIN30: C124.1, J31.3, R61.2, U31.3
VIN31: C128.1, J32.3, R63.2, U32.3
VIN32: C132.1, J33.3, R65.2, U33.3
VIN33: C136.1, J34.3, R67.2, U34.3
VIN34: C140.1, J35.3, R69.2, U35.3
VIN35: C144.1, J36.3, R71.2, U36.3
VIN36: C148.1, J37.3, R73.2, U37.3
VIN37: C152.1, J38.3, R75.2, U38.3
VIN38: C156.1, J39.3, R77.2, U39.3
VIN39: C160.1, J40.3, R79.2, U40.3
VIN40: C164.1, J41.3, R81.2, U41.3
VIN41: C168.1, J42.3, R83.2, U42.3
VIN42: C172.1, J43.3, R85.2, U43.3
VIN43: C176.1, J44.3, R87.2, U44.3
VIN44: C180.1, J45.3, R89.2, U45.3
VIN45: C184.1, J46.3, R91.2, U46.3
VIN46: C188.1, J47.3, R93.2, U47.3
VIN47: C192.1, J48.3, R95.2, U48.3
VIN48: C196.1, J49.3, R97.2, U49.3
VIN49: C200.1, J50.3, R99.2, U50.3
VIN50: C204.1, J51.3, R101.2, U51.3
VIN51: C208.1, J52.3, R103.2, U52.3
VIN52: C212.1, J53.3, R105.2, U53.3
VIN53: C216.1, J54.3, R107.2, U54.3
VIN54: C220.1, J55.3, R109.2, U55.3
VIN55: C224.1, J56.3, R111.2, U56.3
VIN56: C228.1, J57.3, R113.2, U57.3
VIN57: C232.1, J58.3, R115.2, U58.3
VIN58: C236.1, J59.3, R117.2, U59.3
VIN59: C240.1, J60.3, R119.2, U60.3
VIN60: C244.1, J61.3, R121.2, U61.3
VIN61: C248.1, J62.3, R123.2, U62.3
VIN62: C252.1, J63.3, R125.2, U63.3
VIN63: C256.1, J64.3, R127.2, U64.3
VIN64: C260.1, J65.3, R129.2, U65.3
VIN65: C264.1, J66.3, R131.2, U66.3
VIN66: C268.1, J67.3, R133.2, U67.3
VIN67: C272.1, J68.3, R135.2, U68.3
VIN68: C276.1, J69.3, R137.2, U69.3
VIN69: C280.1, J70.3, R139.2, U70.3
VIN70: C284.1, J71.3, R141.2, U71.3
VIN71: C288.1, J72.3, R143.2, U72.3
VIN72: C292.1, J73.3, R145.2, U73.3
VIN73: C296.1, J74.3, R147.2, U74.3
VIN74: C300.1, J75.3, R149.2, U75.3
VIN75: C304.1, J76.3, R151.2, U76.3
VIN76: C308.1, J77.3, R153.2, U77.3
VIN77: C312.1, J78.3, R155.2, U78.3
VIN78: C316.1, J79.3, R157.2, U79.3
VIN79: C320.1, J80.3, R159.2, U80.3
VIN80: C324.1, J81.3, R161.2, U81.3
VIN81: C328.1, J82.3, R163.2, U82.3
VIN82: C332.1, J83.3, R165.2, U83.3
VIN83: C336.1, J84.3, R167.2, U84.3
VIN84: C340.1, J85.3, R169.2, U85.3
VIN85: C344.1, J86.3, R171.2, U86.3
VIN86: C348.1, J87.3, R173.2, U87.3
VIN87: C352.1, J88.3, R175.2, U88.3
VIN88: C356.1, J89.3, R177.2, U89.3
VIN89: C360.1, J90.3, R179.2, U90.3
VIN90: C364.1, J91.3, R181.2, U91.3
VIN91: C368.1, J92.3, R183.2, U92.3
VIN92: C372.1, J93.3, R185.2, U93.3
VIN93: C376.1, J94.3, R187.2, U94.3
VIN94: C380.1, J95.3, R189.2, U95.3
VIN95: C384.1, J96.3, R191.2, U96.3
VIN96: C388.1, J97.3, R193.2, U97.3
VIN97: C392.1, J98.3, R195.2, U98.3
VIN98: C396.1, J99.3, R197.2, U99.3
VIN99: C400.1, J100.3, R199.2, U100.3
VIN100: C404.1, J101.3, R201.2, U101.3
VIN101: C408.1, J102.3, R203.2, U102.3
VIN102: C412.1, J103.3, R205.2, U103.3
VIN103: C416.1, J104.3, R207.2, U104.3

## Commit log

2021-05-24 intial commit
2021-05-25 v01 update
    -Added barrel jack
    -Replaced 4.7uF capacitors with 10uF/50V
2021-05-26 v01 post view changes
2021-05-27 Update SparkFun Buck Regulator Breakout - AP63203.sch
    Added led jumper note
2021-05-27 Added panel data
2021-06-01 BabyBuck Panel Update
    Reduced panel size
2021-06-30 Updated barrel jack silk
